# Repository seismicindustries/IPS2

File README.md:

# IPS2
the infamous interruptible power supply is back
version 2 with usbC and more mmpfh (700mA@12V / 500mA@-12V)

source files for the PCB and .step file for the frontpanel
feel free to use for your own - no groupbuys please.
ask me if you wanna buy a panel & pcb. im gonna make some.

License
=======
CC-BY-SA-NC license

by seismic industries / 2019

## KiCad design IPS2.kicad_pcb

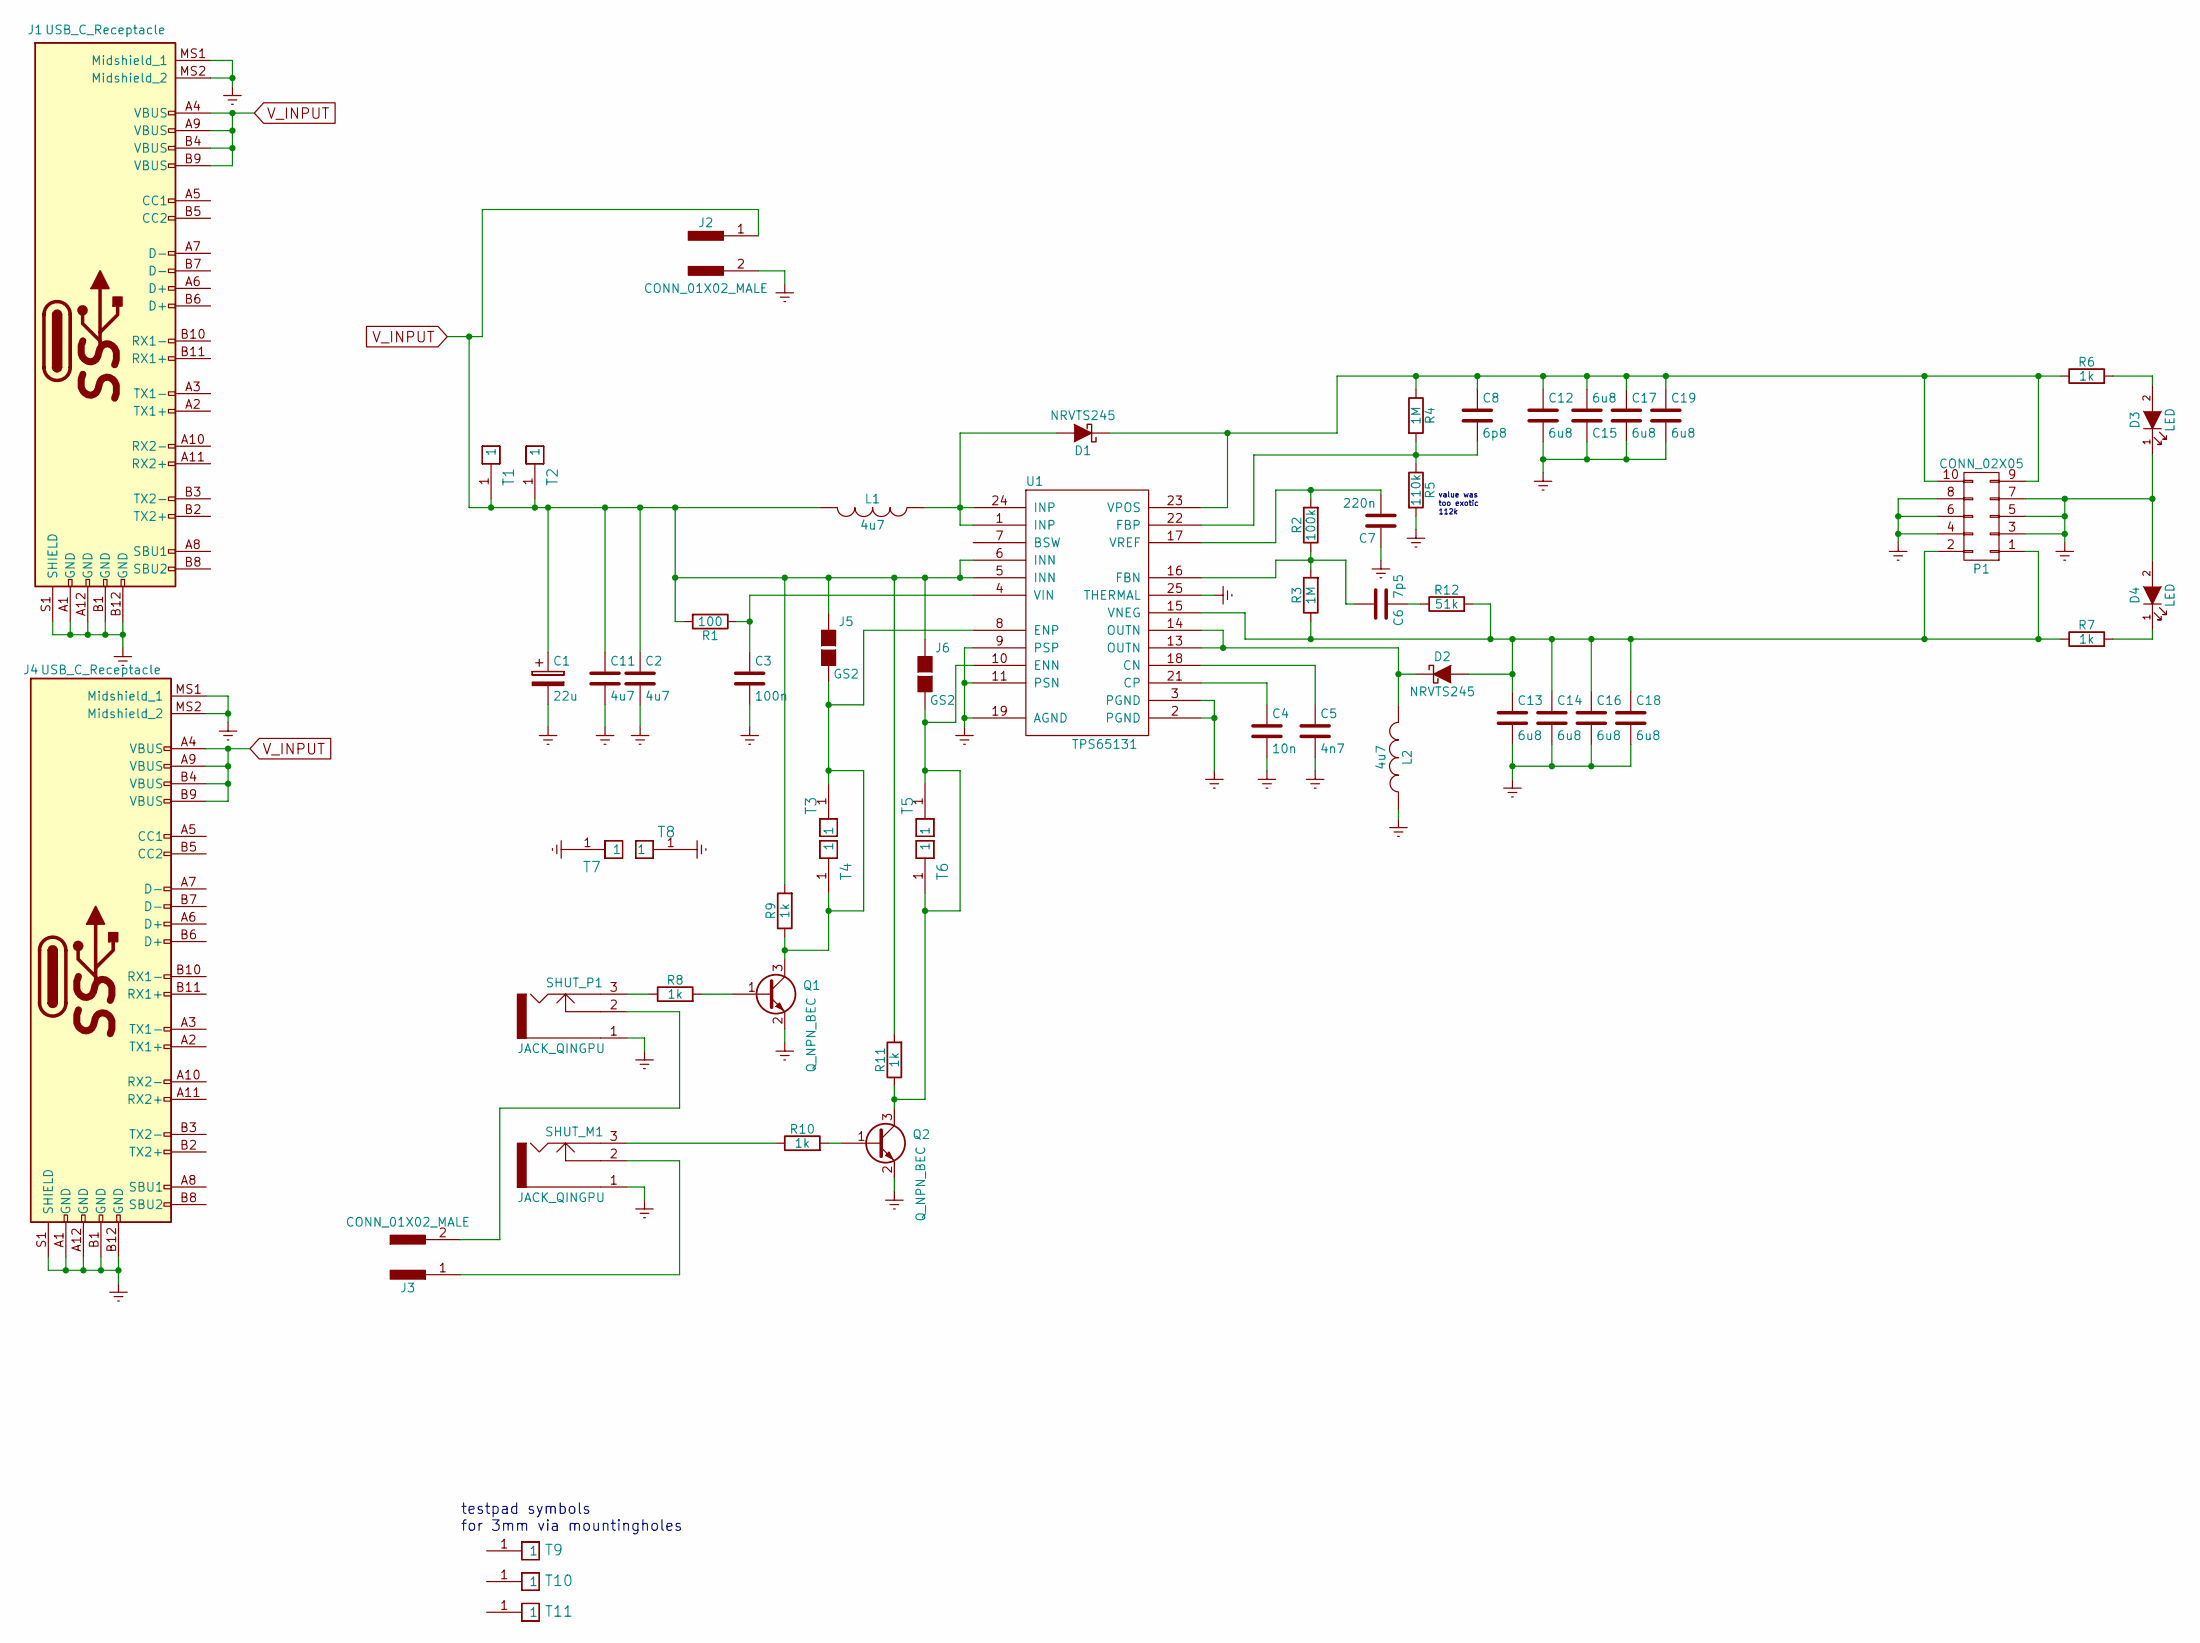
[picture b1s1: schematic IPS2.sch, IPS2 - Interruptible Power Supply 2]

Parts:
C1: 22u; CP_Elec_7.3x4.3; MPN EEF-CX1D220R
C2, C11: 4u7; C_0805; MPN GRM21BR61H475KE51L
C3: 100n; C_0603; MPN C0603C104Z3VACTU
C4: 10n; C_0603; MPN 885012206065
C5: 4n7; C_0603; MPN 885012206087
C6: 7p5; C_0603; MPN GRM1885C1H7R5BA1D
C7: 220n; C_0603; MPN CC603KRX7R7BB224
C8: 6p8; C_0603; MPN 885012006050
C12, C13, C14, C15, C16, C17, C18, C19: 6u8; C_1206; MPN C3216X7R1E685K160AB
D1, D2: NRVTS245; D_SOD-123F; MPN NRVTS245ESFT3G
D3, D4: LED; C_0805; MPN APT2012SGC
J1, J4: USB_C_Receptacle; USB_TYPE_C_WUERTH_632723300011; MPN 632723300011
J2: CONN_01X02_MALE; Pin_Header_Angled_1x02_Pitch2.54mm
J3: CONN_01X02_MALE; Pin_Header_Angled_2x01_Pitch2.54mm
J5, J6: GS2
L1, L2: 4u7; Inductor_SRN4018TA_bourns; MPN SRN4018TA-4R7M
P1: CONN_02X05; Pin_Header_Angled_2x05_Pitch2.54mm_with_space_for_con; MPN 649-68020-110HLF
Q1, Q2: Q_NPN_BEC; SOT-23; MPN BC847CLT1G
R1: 100; R_0603; MPN CRCW0603100RFKEAC
R2: 100k; R_0603; MPN RCA0603100KJNEC
R3, R4: 1M; R_0603; MPN RC0603FR-071ML
R5: 110k; R_0603; MPN CR0603-FX-1103ELF
R6, R7, R8, R9, R10, R11: 1k; R_0603; MPN RC0603FR-071KL
R12: 51k; R_0603; MPN RC0603FR-0751KL
SHUT_M1: JACK_QINGPU; jack_qingpu
SHUT_P1: JACK_QINGPU; jack_qingpu
T1, T2, T3, T4, T5, T6, T7, T8: TESTPIN; TESTPAD_SMD_and_THT_SQR
T9, T10, T11: TESTPIN; VIA_M3_mounting_hole
U1: TPS65131; QFN-24-4x4mm_Pitch0.5mm_handsolder_big_thermal_hole; MPN TPS65131RGER

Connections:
Earth: C1.2, C2.2, C3.2, C4.2, C5.2, C7.1, C11.2, C12.2, C13.2, C14.2, C15.1, C16.2, C17.2, C18.2, C19.2, D3.1 (K), D4.2 (A), J1.A1 (GND), J1.A12 (GND), J1.B1 (GND), J1.B12 (GND), J1.MS1 (Midshield_1), J1.MS2 (Midshield_2), J1.S1 (SHIELD), J2.2, J4.A1 (GND), J4.A12 (GND), J4.B1 (GND), J4.B12 (GND), J4.MS1 (Midshield_1), J4.MS2 (Midshield_2), J4.S1 (SHIELD), L2.1, P1.3, P1.4, P1.5, P1.6, P1.7, P1.8, Q1.2 (E), Q2.2 (E), R5.2, SHUT_M1.1, SHUT_P1.1, T7.1, T8.1, U1.2 (PGND), U1.3 (PGND), U1.9 (PSP), U1.11 (PSN), U1.19 (AGND), U1.25 (THERMAL)
unnamed: C3.1, R1.1, U1.4 (VIN)
unnamed: C4.1, U1.21 (CP)
unnamed: C5.1, U1.18 (CN)
unnamed: C6.1, R12.1
unnamed: C6.2, R2.1, R3.2, U1.16 (FBN)
unnamed: C7.2, R2.2, U1.17 (VREF)
unnamed: C8.2, R4.2, R5.1, U1.22 (FBP)
unnamed: C8.1, C12.1, C15.2, C17.1, C19.1, D1.1 (K), P1.9, P1.10, R4.1, R6.1, U1.23 (VPOS)
unnamed: C13.1, C14.1, C16.1, C18.1, D2.2 (A), P1.1, P1.2, R3.1, R7.1, R12.2, U1.15 (VNEG)
unnamed: D1.2 (A), L1.1, U1.1 (INP), U1.24 (INP)
unnamed: D2.1 (K), L2.2, U1.13 (OUTN), U1.14 (OUTN)
unnamed: D3.2 (A), R6.2
unnamed: D4.1 (K), R7.2
unnamed: J3.1, SHUT_M1.2
unnamed: J3.2, SHUT_P1.2
unnamed: J5.2 (G2), Q1.3 (C), R9.1, T3.1, T4.1, U1.8 (ENP)
unnamed: J6.2 (G2), Q2.3 (C), R11.1, T5.1, T6.1, U1.10 (ENN)
unnamed: Q1.1 (B), R8.2
unnamed: Q2.1 (B), R10.2
unnamed: R8.1, SHUT_P1.3
unnamed: R10.1, SHUT_M1.3
V_INPUT: C1.1, C2.1, C11.1, J1.A4 (VBUS), J1.A9 (VBUS), J1.B4 (VBUS), J1.B9 (VBUS), J2.1, J4.A4 (VBUS), J4.A9 (VBUS), J4.B4 (VBUS), J4.B9 (VBUS), J5.1 (G1), J6.1 (G1), L1.2, R1.2, R9.2, R11.2, T1.1, T2.1, U1.5 (INN), U1.6 (INN)

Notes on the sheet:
testpad symbols for 3mm via mountingholes
value was too exotic 112k

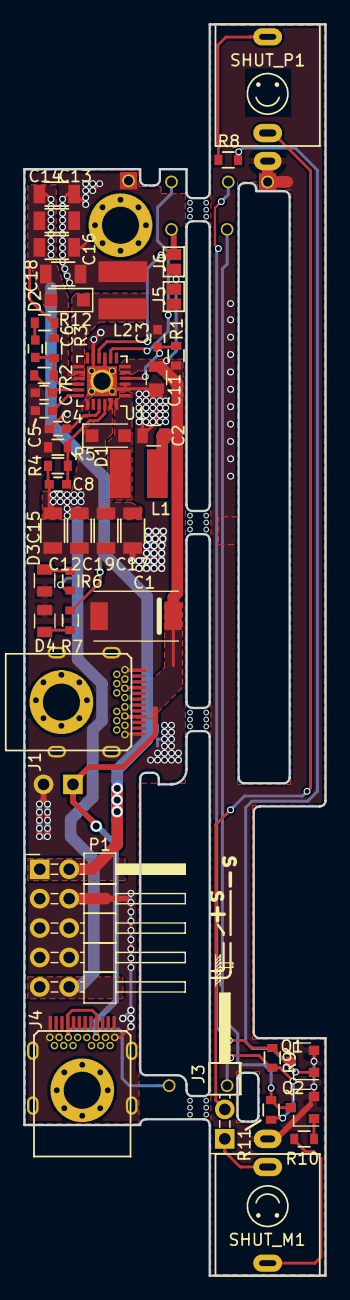
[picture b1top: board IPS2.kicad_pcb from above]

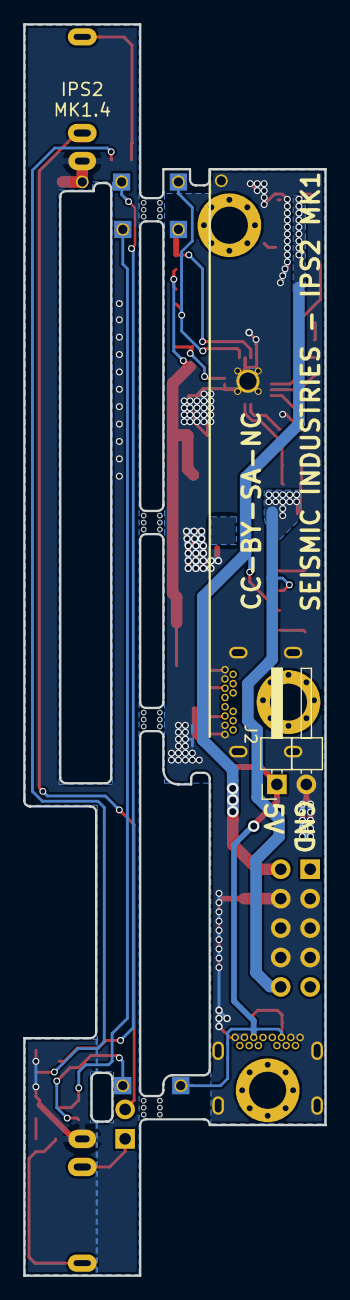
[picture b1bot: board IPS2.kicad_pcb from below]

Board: 2 copper layers, 26.0 x 108.0 mm, 58 parts (7 on the bottom side), 23 nets.

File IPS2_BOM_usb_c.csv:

Refs,Value,Footprint,QTY,MFR,MPN,SPR,SPN
J6;J5,GS2,Connectors:GS2,2,,,,
C1,22u,raffilibkicad:CP_Elec_7.3x4.3,1,Panasonic,EEF-CX1D220R,Mouser,667-EEF-CX1D220R
C3,100n,raffilibkicad:C_0603,1,Kemet,C0603C104Z3VACTU,Mouser,80-C0603C104Z3V
C4,10n,raffilibkicad:C_0603,1,Wuerth,885012206065,Mouser,710-885012206065
C7,220n,raffilibkicad:C_0603,1,Yageo,CC603KRX7R7BB224,Mouser,603-CC603KRX7R7BB224
C5,4n7,raffilibkicad:C_0603,1,Wuerth,885012206087,Mouser,710-885012206087
C8,6p8,raffilibkicad:C_0603,1,Wuerth,885012006050,Mouser,710-885012006050
C6,7p5,raffilibkicad:C_0603,1,Murata,GRM1885C1H7R5BA1D,Mouser,81-GRM1885C1H7R5BA1D
C2;C11,4u7,raffilibkicad:C_0805,2,Murata,GRM21BR61H475KE51L,Mouser,81-GRM21BR61H475KE1L
D3;D4,LED,raffilibkicad:C_0805,2,Kingbright,APT2012SGC,Mouser,604-APT2012SGC
C12;C15;C17;C19;C13;C14;C16;C18,6u8,raffilibkicad:C_1206,8,TDK,C3216X7R1E685K160AB,Mouser,810-C3216X7R1E685K
D1;D2,NRVTS245,raffilibkicad:D_SOD-123F,2,ON Semiconductor,NRVTS245ESFT3G,Mouser,863-NRVTS245ESFT3G
L1;L2,4u7,raffilibkicad:Inductor_SRN4018TA_bourns,2,Bourns,SRN4018TA-4R7M,Mouser,652-SRN4018TA-4R7M
J2,CONN_01X02_MALE,raffilibkicad:Pin_Header_Angled_1x02_Pitch2.54mm,1,,,,
J3,CONN_01X02_MALE,raffilibkicad:Pin_Header_Angled_2x01_Pitch2.54mm,1,,,,
P1,CONN_02X05,raffilibkicad:Pin_Header_Angled_2x05_Pitch2.54mm_with_space_for_con,1,Amphenol FCI,649-68020-110HLF,Mouser,68020-110HLF
U1,TPS65131,raffilibkicad:QFN-24-4x4mm_Pitch0.5mm_handsolder_big_thermal_hole,1,Texas,TPS65131RGER,Mouser,595-TPS65131RGER
R1,100,raffilibkicad:R_0603,1,Vishay,CRCW0603100RFKEAC,Mouser,71-CRCW0603100RFKEAC
R2,100k,raffilibkicad:R_0603,1,Vishay / Draloric,RCA0603100KJNEC,Mouser,71-RCA0603100KJNEC
R5,110k,raffilibkicad:R_0603,1,Bourns,CR0603-FX-1103ELF,Mouser,652-CR0603FX-1103ELF
R4;R3,1M,raffilibkicad:R_0603,2,Yageo,RC0603FR-071ML,Mouser,603-RC0603FR-071ML
R6;R7;R9;R11;R8;R10,1k,raffilibkicad:R_0603,6,Yageo,RC0603FR-071KL,Mouser,603-RC0603FR-071KL
R12,51k,raffilibkicad:R_0603,1,Yageo,RC0603FR-0751KL,Mouser,603-RC0603FR-0751KL
Q1;Q2,Q_NPN_BEC,raffilibkicad:SOT-23,2,ON Semiconductor,BC847CLT1G,Mouser,863-BC847CLT1G
T2;T1;T3;T4;T5;T6;T7;T8,TESTPIN,raffilibkicad:TESTPAD_SMD_and_THT_SQR,8,,,,
J1;J4,USB_C_Receptacle,raffilibkicad:USB_TYPE_C_WUERTH_632723300011,2,Wurth ,632723300011,Mouser,710-632723300011
T9;T10;T11,TESTPIN,raffilibkicad:VIA_M3_mounting_hole,3,,,,
SHUT_P1;SHUT_M1,JACK_QINGPU,raffilibkicad:jack_qingpu,2,,,,

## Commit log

2019-10-16 first commit - added all files and pic to the repo
2019-10-16 resized images
2019-10-16 added panel .step file
2019-11-30 added BOM as csv
